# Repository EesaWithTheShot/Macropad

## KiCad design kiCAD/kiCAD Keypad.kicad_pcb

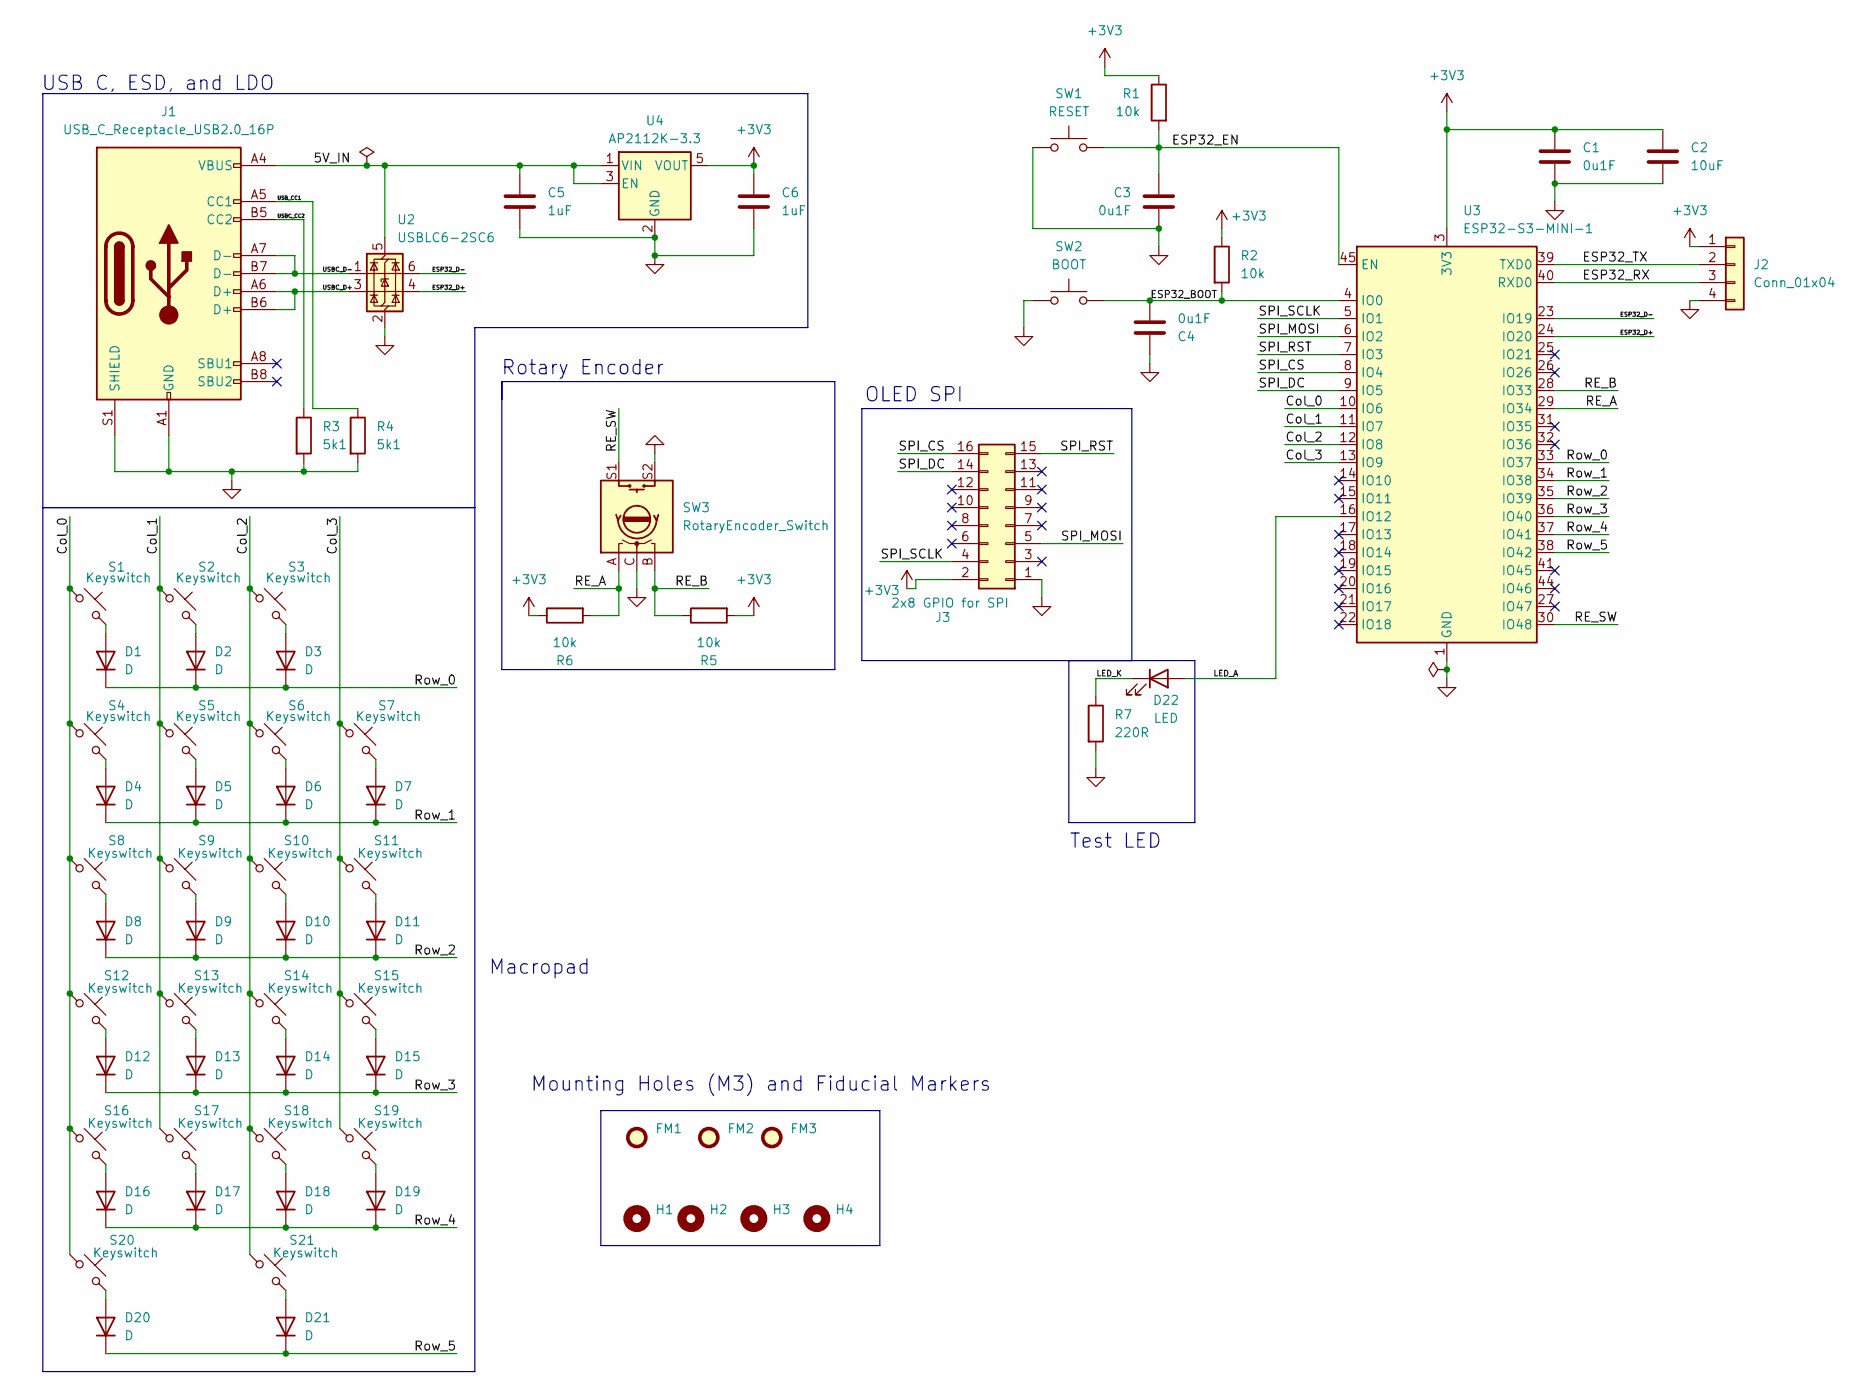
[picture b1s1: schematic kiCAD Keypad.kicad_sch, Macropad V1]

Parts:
C1, C3, C4: 0u1F; C_0402_1005Metric; LCSC C1525
C2: 10uF; C_0805_2012Metric; Manufacturer Part Number GRM21BR61C106KE15K; LCSC C408141
C5, C6: 1uF; C_0805_2012Metric; Manufacturer Part Number 0805B105K500NT; LCSC C215803
D1, D2, D3, D4, D5, D6, D7, D8, D9, D10, D11, D12, D13, D14, D15, D16, D17, D18, D19, D20, D21: D; Diode_DO-35; Manufacturer Part Number 1N4148
D22: LED; LED_0402_1005Metric; Manufacturer Part Number 150040RS73240; LCSC C2984137
FM1, FM2, FM3: Fiducial; Fiducial_1mm_Mask2mm
H1, H2, H3, H4: MountingHole; MountingHole_2.2mm_M2
J1: USB_C_Receptacle_USB2.0_16P; USB_C_Receptacle_GCT_USB4105-xx-A_16P_TopMnt_Horizontal; Manufacturer Part Number USB4105-GF-A; LCSC C3025063
J2: Conn_01x04; PinHeader_1x04_P2.54mm_Vertical; LCSC C5116483
J3: 2x8 GPIO for SPI; PinSocket_2x08_P2.54mm_Vertical_SMD; Manufacturer Part Number NPTC082KFMS-RC; LCSC C157340
R1, R2, R5, R6: 10k; R_0402_1005Metric; Manufacturer Part Number RC0603FR-0710KL; LCSC C98220
R3, R4: 5k1; R_0402_1005Metric; Manufacturer Part Number RC0603FR-075K1L; LCSC C105580
R7: 220R; R_0402_1005Metric; Manufacturer Part Number RC0402FR-07221RL; LCSC C185440
S1, S2, S3, S4, S5, S6, S7, S8, S9, S10, S11, S12, S13, S14, S15, S16, S17, S18, S21: Keyswitch; Hotswap_MX_1.00u; Manufacturer Part Number MMD Princess Tactiles
S19: Keyswitch; Hotswap_MX_2.00u_90deg; Manufacturer Part Number MMD Princess Tactiles
S20: Keyswitch; Hotswap_MX_2.00u; Manufacturer Part Number MMD Princess Tactiles
SW1: RESET; SW_SPST_PTS647_Sx50; Manufacturer Part Number PTS647SN50SMTR2 LFS; LCSC C2799414
SW2: BOOT; SW_SPST_PTS647_Sx50; Manufacturer Part Number PTS647SN50SMTR2 LFS; LCSC C2799414
SW3: RotaryEncoder_Switch; XDCR_PEC11R-4215F-S0024; Manufacturer Part Number PEC11R-4215F-S0024; LCSC C143790
U2: USBLC6-2SC6; SOT-23-6; Manufacturer Part Number USBLC6-2SC6; LCSC C2827654
U3: ESP32-S3-MINI-1; ESP32-S2-MINI-1; Manufacturer Part Number ESP32-S3-MINI-1-N8; LCSC C2913206
U4: AP2112K-3.3; SOT-23-5; Manufacturer Part Number AP2112K-3.3TRG1; LCSC C51118

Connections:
+3V3: C1.1, C2.1, C6.1, J2.1, J3.2, R1.1, R2.1, R5.2, R6.1, U3.3 (3V3), U4.5 (VOUT)
/5V_IN: C5.1, J1.A4 (VBUS), J1.A9 (VBUS), J1.B4 (VBUS), J1.B9 (VBUS), U2.5 (VBUS), U4.1 (VIN), U4.3 (EN)
/Col_0: S1.1, S4.1, S8.1, S12.1, S16.1, S20.1, U3.10 (IO6)
/Col_1: S2.1, S5.1, S9.1, S13.1, S17.1, U3.11 (IO7)
/Col_2: S3.1, S6.1, S10.1, S14.1, S18.1, S21.1, U3.12 (IO8)
/Col_3: S7.1, S11.1, S15.1, S19.1, U3.13 (IO9)
/ESP32_BOOT: C4.2, R2.2, SW2.2, U3.4 (IO0)
/ESP32_D+: U2.4 (I/O2), U3.24 (IO20)
/ESP32_D-: U2.6 (I/O1), U3.23 (IO19)
/ESP32_EN: C3.1, R1.2, SW1.1, U3.45 (EN)
/ESP32_RX: J2.3, U3.40 (RXD0)
/ESP32_TX: J2.2, U3.39 (TXD0)
/LED_A: D22.2 (A), U3.16 (IO12)
/LED_K: D22.1 (K), R7.1
/RE_A: R6.2, SW3.A, U3.29 (IO34)
/RE_B: R5.1, SW3.B, U3.28 (IO33)
/RE_SW: SW3.S1, U3.30 (IO48)
/Row_0: D1.1 (K), D2.1 (K), D3.1 (K), U3.33 (IO37)
/Row_1: D4.1 (K), D5.1 (K), D6.1 (K), D7.1 (K), U3.34 (IO38)
/Row_2: D8.1 (K), D9.1 (K), D10.1 (K), D11.1 (K), U3.35 (IO39)
/Row_3: D12.1 (K), D13.1 (K), D14.1 (K), D15.1 (K), U3.36 (IO40)
/Row_4: D16.1 (K), D17.1 (K), D18.1 (K), D19.1 (K), U3.37 (IO41)
/Row_5: D20.1 (K), D21.1 (K), U3.38 (IO42)
/SPI_CS: J3.16, U3.8 (IO4)
/SPI_DC: J3.14, U3.9 (IO5)
/SPI_MOSI: J3.5, U3.6 (IO2)
/SPI_RST: J3.15, U3.7 (IO3)
/SPI_SCLK: J3.4, U3.5 (IO1)
/USBC_CC2: J1.B5 (CC2), R3.1
/USBC_D+: J1.A6 (D+), J1.B6 (D+), U2.3 (I/O2)
/USBC_D-: J1.A7 (D-), J1.B7 (D-), U2.1 (I/O1)
/USB_CC1: J1.A5 (CC1), R4.1
GND: C1.2, C2.2, C3.2, C4.1, C5.2, C6.2, J1.A1 (GND), J1.A12 (GND), J1.B1 (GND), J1.B12 (GND), J1.S1 (SHIELD), J2.4, J3.1, R3.2, R4.2, R7.2, SW1.2, SW2.1, SW3.C, SW3.S2, U2.2 (GND), U3.1 (GND), U3.2 (GND), U3.42 (GND), U3.43 (GND), U3.46 (GND), U3.47 (GND), U3.48 (GND), U3.49 (GND), U3.50 (GND), U3.51 (GND), U3.52 (GND), U3.53 (GND), U3.54 (GND), U3.55 (GND), U3.56 (GND), U3.57 (GND), U3.58 (GND), U3.59 (GND), U3.60 (GND), U3.61 (GND), U3.62 (GND), U3.63 (GND), U3.64 (GND), U3.65 (GND), U4.2 (GND)
unnamed: D1.2 (A), S1.2
unnamed: D2.2 (A), S2.2
unnamed: D3.2 (A), S3.2
unnamed: D4.2 (A), S4.2
unnamed: D5.2 (A), S5.2
unnamed: D6.2 (A), S6.2
unnamed: D7.2 (A), S7.2
unnamed: D8.2 (A), S8.2
unnamed: D9.2 (A), S9.2
unnamed: D10.2 (A), S10.2
unnamed: D11.2 (A), S11.2
unnamed: D12.2 (A), S12.2
unnamed: D13.2 (A), S13.2
unnamed: D14.2 (A), S14.2
unnamed: D15.2 (A), S15.2
unnamed: D16.2 (A), S16.2
unnamed: D17.2 (A), S17.2
unnamed: D18.2 (A), S18.2
unnamed: D19.2 (A), S19.2
unnamed: D20.2 (A), S20.2
unnamed: D21.2 (A), S21.2

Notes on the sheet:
Test LED
Rotary Encoder
Macropad
Mounting Holes (M3) and Fiducial Markers
OLED SPI
USB C, ESD, and LDO

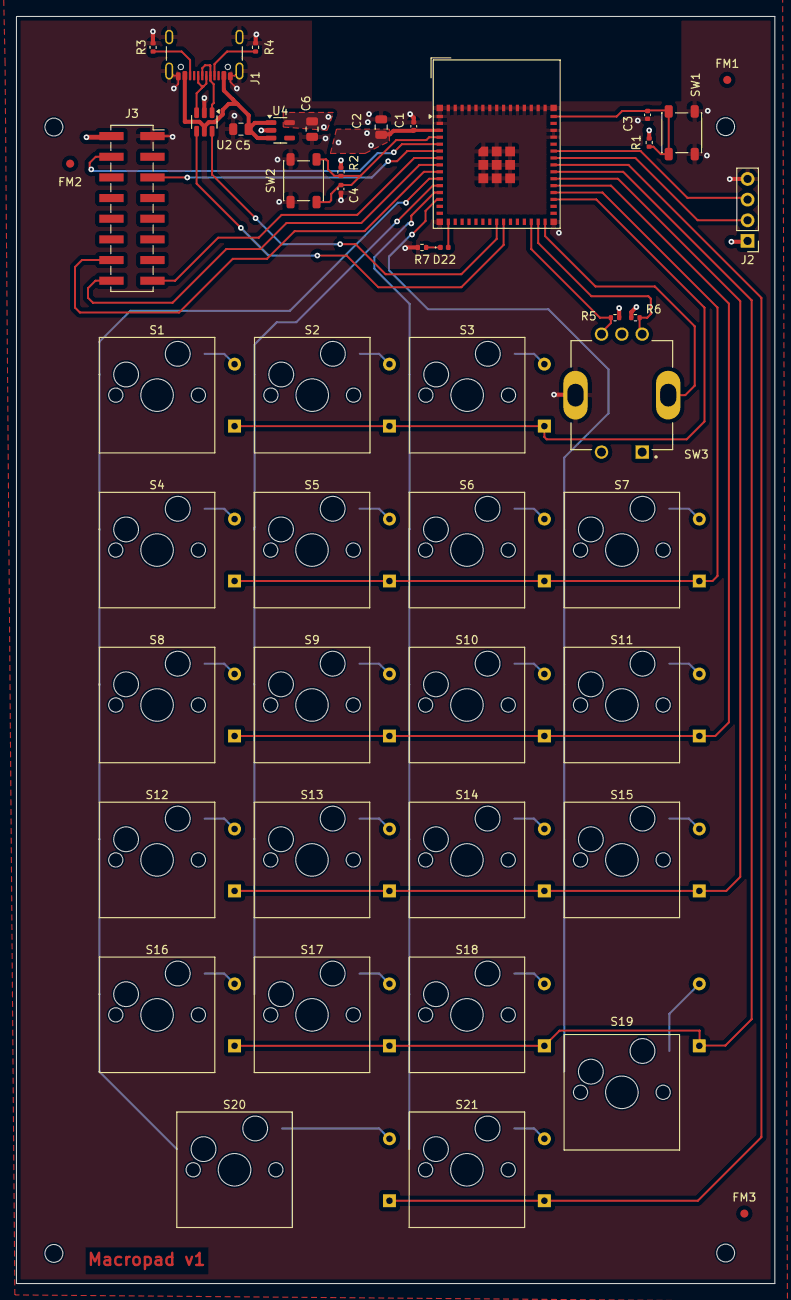
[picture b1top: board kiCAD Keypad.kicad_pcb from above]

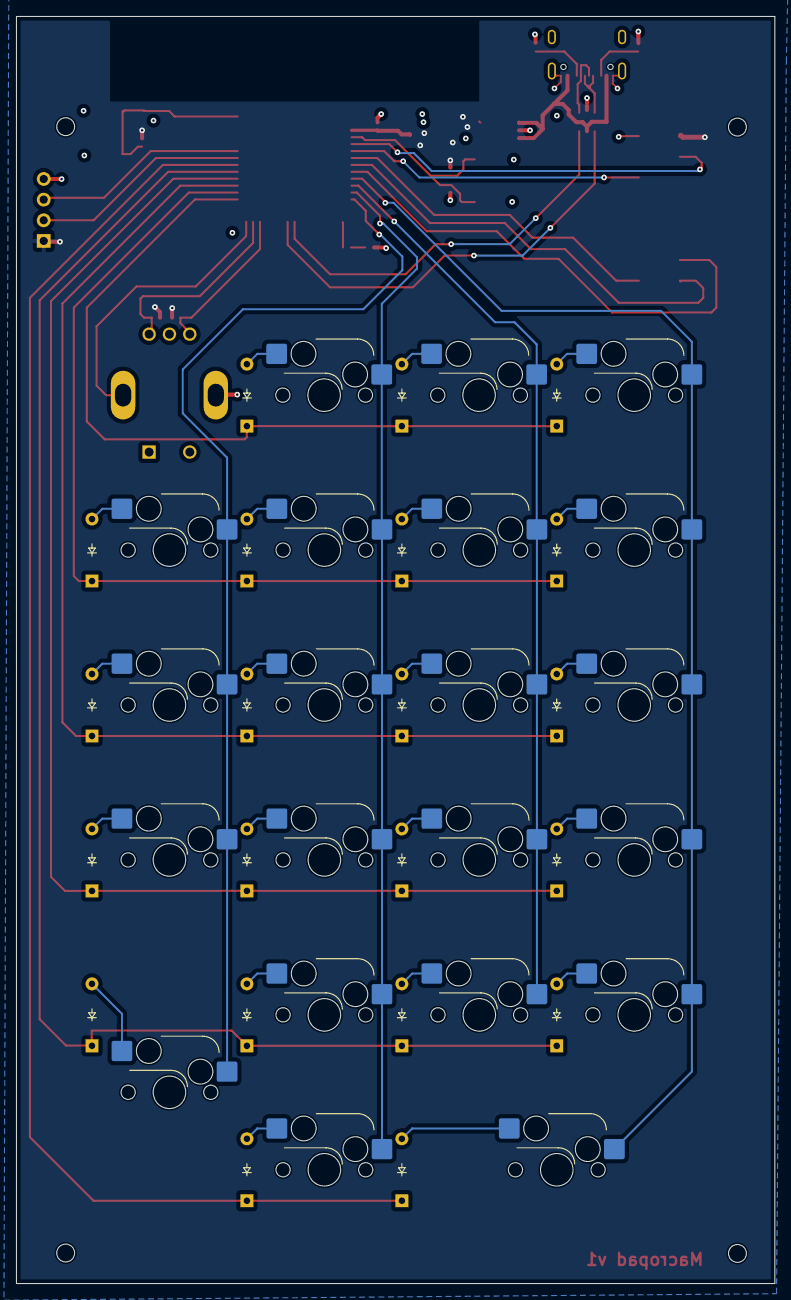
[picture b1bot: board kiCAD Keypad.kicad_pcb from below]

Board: 4 copper layers, 93.2 x 155.8 mm, 72 parts (21 on the bottom side), 54 nets.

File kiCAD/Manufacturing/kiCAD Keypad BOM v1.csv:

Designator,Comment,Footprint,Qty,LCSC Part Number
"C1,C3,C4",0u1F,Capacitor_SMD:C_0402_1005Metric,3,C1525
C2,10uF,Capacitor_SMD:C_0805_2012Metric,1,C408141
"C5,C6",1uF,Capacitor_SMD:C_0805_2012Metric,2,C215803
D22,LED,LED_SMD:LED_0402_1005Metric,1,C2984137
J1,USB_C_Receptacle_USB2.0_16P,Connector_USB:USB_C_Receptacle_GCT_USB4105-xx-A_16P_TopMnt_Horizontal,1,C3025063
J2,Conn_01x04,Connector_PinHeader_2.54mm:PinHeader_1x04_P2.54mm_Vertical,1,C5116483
J3,2x8 GPIO for SPI,Connector_PinSocket_2.54mm:PinSocket_2x08_P2.54mm_Vertical_SMD,1, C157340
"R1,R2,R5,R6",10k,Resistor_SMD:R_0402_1005Metric,4,C98220
"R3,R4",5k1,Resistor_SMD:R_0402_1005Metric,2,C105580
R7,220R,Resistor_SMD:R_0402_1005Metric,1,C185440
"SW1,SW2","RESET, BOOT",Button_Switch_SMD:SW_SPST_PTS647_Sx50,1,C2799414
SW3,RotaryEncoder_Switch,Macropad_Libs:XDCR_PEC11R-4215F-S0024,1,C143790
U2,USBLC6-2SC6,Package_TO_SOT_SMD:SOT-23-6,1,C2827654
U3,ESP32-S3-MINI-1,RF_Module:ESP32-S2-MINI-1,1,C2913206
U4,AP2112K-3.3,Package_TO_SOT_SMD:SOT-23-5,1,C51118

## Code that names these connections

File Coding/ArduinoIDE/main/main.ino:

#include <U8g2lib.h>
#include <string>

// all the adssigned pins on the board
// Left side
#define EXTRA_PIN (6)
#define DC_PIN (8)
#define CS_PIN (17)
#define RST_PIN (20)
#define COL_0_PIN (22)
#define COL_1_PIN (24)
#define COL_2_PIN (32)
#define COL_3_PIN (11)
#define RE_A_PIN (36)
#define RE_B_PIN (38)
// Right Side
#define ROW_5_PIN (31)
#define ROW_4_PIN (29)
#define ROW_3_PIN (2)
#define ROW_2_PIN (47)
#define SCK_PIN (45)
#define ROW_1_PIN (43)
#define MOSI_PIN (10)
#define ROW_0_PIN (9)

U8G2_SSD1322_NHD_256X64_F_4W_HW_SPI u8g2(U8G2_R0, /* cs=*/CS_PIN, /* dc=*/DC_PIN, /* reset=*/RST_PIN);

void setup(void) {
  Serial.begin(115200);
  u8g2.begin();

  Serial.println("Successfully Initialized");
}

void loop(void) {
  u8g2.clearBuffer();                                   // clear the internal memory
  u8g2.setFont(u8g2_font_ncenB08_tr);                   // choose a suitable font
  u8g2.drawStr(0, 10, "Hello World! My name is eESA");  // write something to the internal memory
  u8g2.sendBuffer();                                    // transfer internal memory to the display
  delay(1000);
  // u8g2.clearBuffer();           // Clear the internal buffer
  // u8g2.drawBox(0, 0, 256, 64);  // Draw a box that fills the entire display
  // u8g2.sendBuffer();            // Send the buffer to the display
  // delay(1000);
}

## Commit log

2024-12-02 Initial Commit (midway through tracing)
2024-12-07 V1 before reddit audit
2024-12-09 Exporting to JLCPCB
2024-12-11 Iterating; deciding on switching to devkit
2024-12-23 Begun coding and also v2 of macropad design
2025-01-07 finished soldering parts
